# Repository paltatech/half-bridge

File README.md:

# TO247 Inverter power stage
This is the hardware repository of a 3 phase inverter, UNTESTED but designed with the following specs in mind:

* 70kw nominal, 150kw peak
* TO247 IGBT to allow for easy silicon upgrades and power capabilities. Its also cheaper.
* Watercooled
* Embedded security features (desaturation, soft turn off, reinforced isolation)

You can also check the layout [here](https://eyrie.io/board?id=7261e811b9074e0fb00fe3fcbbaa14d9) 

Will need some cnc milling, components, a pcb, and some spot welding

Made open source with open source tools (kicad, freecad)

## Bill of materials
BOM, pcb gerbers, and custom parts can be found in [fabrication files](https://bitbucket.org/paltatech/half-bridge) directory

## License
This documentation describes Open Hardware and is licensed under the CERN OHL v. 1.2

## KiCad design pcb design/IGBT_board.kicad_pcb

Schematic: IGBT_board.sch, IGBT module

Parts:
C1, C2, C3, C4, C5, C6, C7: 16uF 700v; CAP_FILM_EPCOS_42x20mm_3D_only; mfg# B32796G3166K
C51, C52: 4.7uF; CAPC2012X70
C77, C82: 100pF; CAPC1608X55
C85: 1uF; CAPC1608X55
D19: TVS; Diode-SMB_Standard; mfg# SMBJ24A
DS1: FAULT; LED-0603
DS2: PWR_GOOD; LED-0603
DS3: RESET; LED-0603
F1: FUSE; RESC3216X60; mfg# 0ZCJ0050AF2E
J1: CONN-100MIL-M-2x8; MPN 5103310-3
J5: PHASE CURRENT CONN; TE-292227-4; MPN 292227-4
MP1: HEATSINK; heatsink-watercooled-20x210mm
Q1, Q2, Q3, Q4, Q5, Q6, Q7, Q8, Q9, Q10, Q11, Q12: IGBT; TO-247-HV; mfg# IXXX110N65B4H1
R1, R2: 1R; RESC3225X60
R3, R4, R5, R6, R7, R8, R9, R10, R11, R12, R13, R14, R15, R16, R17, R18, R19, R20, R21, R22, R23, R24: 20R; RESC3225X60; mfg# CRCW251220R0FKEG
R51, R52, R53: 1k; RESC1608X50
R54, R56, R59, R61: 22R; RESC1608X50
SYM1: OSHW-SCHEM-PCB10mm; Logo_silk_OSHW_12x13mm
U5: LM1117IMP-v.v; SOT-223

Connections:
+5: C52.1, C85.2, J5.1, R51.1, R52.1, R53.1, U5.2, U5.4; also elsewhere on the board
+24: C51.1, D19.1, F1.2, U5.3; also elsewhere on the board
/FAULT: DS1.1, R61.2; also elsewhere on the board
/I_phase+: J1.2, J5.2
/I_phase-: J1.1, J5.3
/PWM_N: C77.1, R54.2; also elsewhere on the board
/PWM_P: C82.2, R59.2; also elsewhere on the board
/PWR_GOOD: DS2.1; also elsewhere on the board
/RESET: DS3.1, R56.1; also elsewhere on the board
/SYNC: J1.8; also elsewhere on the board
/TEMP: J1.9
/VEE_CTRL: J1.7; also elsewhere on the board
/V_phase+: J1.4; also elsewhere on the board
/V_phase-: J1.3; also elsewhere on the board
GATE_HIGH: R1.1, R2.1, R5.1, R6.1, R9.1, R10.1, R13.1, R14.1, R17.1, R18.1, R21.1, R22.1; also elsewhere on the board
GATE_LOW: R3.1, R4.1, R7.1, R8.1, R11.1, R12.1, R15.1, R16.1, R19.1, R20.1, R23.1, R24.1; also elsewhere on the board
GND: C51.2, C52.2, C77.2, C82.1, C85.1, D19.2, J1.10, J1.14, J1.16, J5.4, U5.1; also elsewhere on the board
unnamed: DS1.2, R51.2
unnamed: DS2.2, R52.2
unnamed: DS3.2, R53.2
unnamed: F1.1, J1.13, J1.15
unnamed: J1.5, R56.2
unnamed: J1.6, R61.1
unnamed: J1.11, R59.1
unnamed: J1.12, R54.1
unnamed: Q1.1, R1.2, R2.2
unnamed: Q2.1, R3.2, R4.2
unnamed: Q3.1, R5.2, R6.2
unnamed: Q4.1, R7.2, R8.2
unnamed: Q5.1, R9.2, R10.2
unnamed: Q6.1, R11.2, R12.2
unnamed: Q7.1, R13.2, R14.2
unnamed: Q8.1, R15.2, R16.2
unnamed: Q9.1, R17.2, R18.2
unnamed: Q10.1, R19.2, R20.2
unnamed: Q11.1, R21.2, R22.2
unnamed: Q12.1, R23.2, R24.2
PHASE: Q1.3, Q2.2, Q3.3, Q4.2, Q5.3, Q6.2, Q7.3, Q8.2, Q9.3, Q10.2, Q11.3, Q12.2; also elsewhere on the board
VBUS+: Q1.2, Q3.2, Q5.2, Q7.2, Q9.2, Q11.2; also elsewhere on the board
VBUS-: Q2.3, Q4.3, Q6.3, Q8.3, Q10.3, Q12.3; also elsewhere on the board

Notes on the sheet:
Highest performance IGBT I found: AUIRGPS4067D1 reasonable performance: IXXX110N65B4H1 tesla used IKW75N60TFKSA1
The plan is to design it for 70kw continuous, 200kw peak So, at 400v you need 175 Amp per phase (70kw current x 2.5). That is 30A per IGBT At 30A, 0.9v Vce = 27W per transistor aim to 50-50 power losses (switching and sat) At 45°C ambient temperature, if we want 75°C Junction temp, its a 30°C dT, a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
Sil-pad thermal: SPK4-0.006-00-11.512 kapton? hard anodized aluminum? gel immersion? (could help with igbt-heatsink cleareances)
Capacitors must be able to supply roughly 65% of battery supplied current, so its important to have enough rms current in the cap bank. In this case, if we plan for 200kW at 500A, we should expect a total RMS current of 325A in the capacitors. We have 16uF*7*3 = 336uF 14Arms per cap -> 98Arms per m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
For BOM creator: kicad_bom_wizard "%I" "%O.csv" "CSV"
(FILM)
PHASE LEG IGBT MODULE
deadtime calculation: * input filter * igbt driver: 30ns(skew)+25ns(rise/fall delta) + * boost transistor: * IGBT:
Rg < Rgdriver / N / 10 for lower Rg mismatch
Use common mode chokes?

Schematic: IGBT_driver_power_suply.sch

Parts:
C17: 1uF; CAPC1608X55
C18: 22nF; CAPC1608X55
C19: 22uF 16v; CAPC2012X70
C20: 1nF; CAPC1608X55
C21: 470pF; CAPC1608X55
C22, C23, C24, C25, C26, C27, C53, C54: 10uF 50v; CAPC3216X70; mfg# CL31A106KBHNNNE
C28, C29, C30, C31: 100nF 50v; CAPC2012X70; mfg# 08055C104JAT2A
C32, C33, C34, C35, C45: 47uF 50v; c_elec_6.3x7.7; mfg# EEE-FK1H470XP
C50: 100pF; CAPC1608X55
D5, D6, D7, D8, D9, D10, D22, D23: RB160MM-60TR; SOD-123F; mfg# RB160MM-60TR
DZ2: MM3Z12VB; SOD-323F; mfg# MM3Z12VB
Q15, Q16: CSD19533Q5A; TEXAS-Q5A; mfg# CSD19533Q5A
R34, R37: 0R; RESC1608X50
R35: 26.7k; RESC1608X50
R36, R40: 1.15k; RESC1608X50
R38, R39: 22R; RESC1608X50
R41: 0.22R; RESC3216X60
T1: TRANS-3-1CT; wurth_750342312; mfg# 750342312
TP1: SW1; TEST-SMD-SMALL
TP2: SW2; TEST-SMD-SMALL
TP6: 24v; TEST-SMD-SMALL
TP7, TP10: 15v; TEST-SMD-SMALL
TP8, TP11: GND; TEST-SMD-SMALL
TP9, TP12: -15v; TEST-SMD-SMALL
U2: LM5030; TSSOP-10_3x3mm_Pitch0.5mm; mfg# LM5030MM/NOPB

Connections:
+24: C45.1, R34.2, R36.1, T1.3, TP6.1; also elsewhere on the board
/IGBT_driver_BOT/+15V: C26.1, C30.1, C34.1, D7.1, TP10.1; also elsewhere on the board
/IGBT_driver_BOT/-15V: C27.2, C31.2, C35.2, D23.2, TP12.1; also elsewhere on the board
/IGBT_driver_TOP/+15V: C24.1, C28.1, C32.1, D5.1, TP7.1; also elsewhere on the board
/IGBT_driver_TOP/-15V: C25.2, C29.2, C33.2, D22.2, TP9.1; also elsewhere on the board
/SYNC: C50.1; also elsewhere on the board
/isolated power supply/CS: C21.1, R40.2, U2.8
GND: C17.1, C18.1, C19.2, C20.2, C21.2, C45.2, DZ2.2, R35.2, R41.2, U2.2, U2.7; also elsewhere on the board
unnamed: C17.2, R34.1, U2.1
unnamed: C18.2, U2.10
unnamed: C19.1, DZ2.1, R36.2, U2.4
unnamed: C20.1, R37.2
unnamed: C22.1, D5.2, D6.1
unnamed: C22.2, C53.2, T1.13
unnamed: C23.1, D7.2, D8.1
unnamed: C23.2, C54.2, T1.8
unnamed: C50.2, R35.1, U2.9
unnamed: C53.1, D9.2, D22.1
unnamed: C54.1, D10.2, D23.1
unnamed: Q15.1, Q15.2, Q15.3, Q16.1, Q16.2, Q16.3, R40.1, R41.1
unnamed: Q15.4, R38.1
unnamed: Q15.5, Q15.6, Q15.7, Q15.8, T1.5, TP1.1
unnamed: Q16.4, R39.2
unnamed: Q16.5, Q16.6, Q16.7, Q16.8, T1.1, TP2.1
unnamed: R37.1, U2.3
unnamed: R38.2, U2.5
unnamed: R39.1, U2.6
PHASE: C24.2, C25.1, C28.2, C29.1, C32.2, C33.1, D6.2, D9.1, T1.14, TP8.1; also elsewhere on the board
VBUS-: C26.2, C27.1, C30.2, C31.1, C34.2, C35.1, D8.2, D10.1, T1.7, TP11.1; also elsewhere on the board

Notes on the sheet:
Power calculation according to http://www.ti.com/lit/ug/tidu355a/tidu355a.pdf 0.6W+(0.000000183C*6)*20000Hz*(15v+8v)+(0.000000005500F*6)*20000Hz*(15v+8v)^2 = 1.45 W
Left side corresponds to http://www.ti.com/lit/ug/tidu355a/tidu355a.pdf Right side corresponds to TIDUA15A
Dual Isolated +15v -15v power supply 2W per IGBT bank
check MGJ2D241509SC
Controlling pwm from MCU could help with harmonics, or maybe sync it with the leg switching freq
Always check the actual capacitance you get at the operating voltage. These curves are for samsung's MLCC caps
weird way to draw a transformer... fix it
About syncing: * External source frequency must be higher than configured frequency (configured with RT) * 15nsec to 150nsec pulse width * 1.5V to 3.0V signal amplitude Why syncing? Phase voltage sampling could be measured at the same point in the power supply ripple. You can avoid switching the su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
Frequency setting with RT. R = (1/F - 172E-9) / 182e-12 So, eval board was switching at 200khz. Figure out why, this transformer is supposed to be operated at 500khz
10k ohm would set this to 500KHz...
For +15/-8v operation, short C53/C54 and remove D9/D10
Ensure <30pF transformer capacitance Less in case of SiC drives.where 5pF will inject 250mA at 50V/ns (dV/dt) in the control side. Adding mounting point for grounding these switching currents to the chassis so they don't travel across control wiring.

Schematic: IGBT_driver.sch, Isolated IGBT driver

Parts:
C8, C83: 100nF; CAPC1608X55
C9, C10, C11: 1uF 50v; CAPC2012X70; mfg# CL21B105KBFNNNE
C12, C13, C57, C58, C71, C72: 10uF 50v; CAPC3216X70; mfg# CL31A106KBHNNNE
C14, C15: 100nF 50v; CAPC2012X70; mfg# 08055C104JAT2A
C16: 100pF COG; CAPC2012X70; mfg# C0805C101J5GACTU
C46: 10uF; CAPC1608X55
C47: 5nF 50v; CAPC2012X70
C55: 1nF; CAPC1608X55
C56: 1uF; CAPC1608X55
C87: 10nF; CAPC1608X55
D1, D16: SK310A-LTP; do214ac; mfg# SK310A-LTP
D2: RB168MM-60TR; SOD-123F; mfg# RB168MM-60TR
D3, D4: MURS160-13-F; Diode-SMB_Standard; mfg# MURS160-13-F
D15: 1N4148W; SOD-123
D17: GSOT03C; SOT-23; mfg# GSOT03C-E3-08
D25: ES2J-LTP; DIOM5226X203; MPN ES2J-LTP
DZ1: MM3Z12VB; SOD-323F; mfg# MM3Z12VB
DZ5: SMCJ440CA; DIOM7959X265; MPN SMCJ440CA
J2: DESAT; CONN-100MIL-F-1x1
Q13: NPN; DPAK-2; mfg# MJD3055T4G
Q14: PNP; DPAK-2; mfg# MJD2955T4G
R25, R26: 10k; RESC1608X50
R27: 10R; RESC1608X50
R28: 4.7k; RESC1608X50
R29, R30: 12R; RESC2012X50
R31, R32: 3R; RESC6432X70; mfg# PCNM2512K3R00FST5
R33: 1k; RESC2012X50
R58: 1k; RESC1608X50
R60: 4.7k; RESC2012X50
R62: 12R; RESC1608X50; mfg# RC0603FR-07390RL
R68, R93: 390R; RESC1608X50; mfg# RC0603FR-07390RL
R69: NI; RESC6432X70
R75: NI; RESC6432X70; MPN PCNM1206K2R00FST5
TP3: IN; TEST-SMD-SMALL
TP4: GND; TEST-SMD-SMALL
U1: ISO5852S; SOIC-16_7.5x10.3mm_Pitch1.27mm; mfg# ISO5852SQDWRQ1
U8: SI8710B; SDIP6; mfg# SI8710BD-B-IS
U13: LM3480; SOT-23; mfg# LM3480IM3X-12/NOPB

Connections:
+5: C46.1, R25.1, R26.1, R27.1; also elsewhere on the board
/FAULT: D15.1, R25.2, U1.13; also elsewhere on the board
/IGBT_driver_TOP/12.0V: C56.1, R68.2, U8.6 (VCC), U13.1 (OUT)
/IGBT_driver_TOP/+15V: C10.1, C12.1, C14.1, C57.1, C71.1, C83.1, D16.1, Q13.2, U1.5, U13.2 (IN); also elsewhere on the board
/IGBT_driver_TOP/-VEE: C9.2, C11.2, C13.2, C15.2, C58.2, C72.2, C87.2, D1.2, Q14.2, U1.1, U1.8; also elsewhere on the board
/IGBT_driver_TOP/supply control/PWM: R68.1, U8.5 (Vo); also elsewhere on the board
/PWM_N: D17.2, R28.1, U1.11; also elsewhere on the board
/PWM_P: D15.2, D17.1, R58.1, TP3.1, U1.10; also elsewhere on the board
/PWR_GOOD: R26.2, U1.12; also elsewhere on the board
/RESET: C55.1, U1.14; also elsewhere on the board
/VEE_CTRL: R93.2; also elsewhere on the board
GATE_HIGH: C47.1, D1.1, D16.2, D25.1, R31.1, R32.1, R60.2, R69.1, R75.1; also elsewhere on the board
GND: C8.2, C46.2, C55.2, D17.3, R28.2, R58.2, TP4.1, U1.9, U1.16, U8.3 (K); also elsewhere on the board
unnamed: C8.1, R27.2, U1.15
unnamed: C16.1, D2.1, DZ1.1, R33.2, U1.2
unnamed: C87.1, R62.1
unnamed: D3.1, D4.2
unnamed: D3.2, R33.1
unnamed: D25.2, DZ5.2
unnamed: Q13.1, Q14.1, R29.1, R30.1
unnamed: Q13.3, R31.2, R69.2
unnamed: Q14.3, R32.2, R75.2
unnamed: R29.2, U1.4
unnamed: R30.2, R62.2, U1.6
unnamed: R93.1, U8.1 (A)
PHASE: C9.1, C10.2, C11.1, C12.2, C13.1, C14.2, C15.1, C16.2, C47.2, C56.2, C57.2, C58.1, C71.2, C72.1, C83.2, D2.2, DZ1.2, R60.1, U1.3, U8.4 (GND), U13.3; also elsewhere on the board
VBUS+: D4.1, DZ5.1, J2.1; also elsewhere on the board

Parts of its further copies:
C36, C84: 100nF; CAPC1608X55
C37, C38, C39: 1uF 50v; CAPC2012X70; mfg# CL21B105KBFNNNE
C40, C41, C65, C66, C73, C74: 10uF 50v; CAPC3216X70; mfg# CL31A106KBHNNNE
C42, C43: 100nF 50v; CAPC2012X70; mfg# 08055C104JAT2A
C44: 100pF COG; CAPC2012X70; mfg# C0805C101J5GACTU
C48: 10uF; CAPC1608X55
C49: 5nF 50v; CAPC2012X70
C63: 1nF; CAPC1608X55
C64: 1uF; CAPC1608X55
C86: 10nF; CAPC1608X55
D11, D18: SK310A-LTP; do214ac; mfg# SK310A-LTP
D12: RB168MM-60TR; SOD-123F; mfg# RB168MM-60TR
D13, D14: MURS160-13-F; Diode-SMB_Standard; mfg# MURS160-13-F
D20: 1N4148W; SOD-123
D21: GSOT03C; SOT-23; mfg# GSOT03C-E3-08
D24: ES2J-LTP; DIOM5226X203; MPN ES2J-LTP
DZ3: MM3Z12VB; SOD-323F; mfg# MM3Z12VB
DZ4: SMCJ440CA; DIOM7959X265; MPN SMCJ440CA
J3: DESAT; CONN-100MIL-F-1x1
Q17: NPN; DPAK-2; mfg# MJD3055T4G
Q18: PNP; DPAK-2; mfg# MJD2955T4G
R42, R43: 10k; RESC1608X50
R44: 10R; RESC1608X50
R45: 4.7k; RESC1608X50
R46, R47: 12R; RESC2012X50
R48, R49: 3R; RESC6432X70; mfg# PCNM2512K3R00FST5
R50: 1k; RESC2012X50
R55: 12R; RESC1608X50; mfg# RC0603FR-07390RL
R57: 1k; RESC1608X50
R67: 4.7k; RESC2012X50
R74, R94: 390R; RESC1608X50; mfg# RC0603FR-07390RL
R89: NI; RESC6432X70
R90: NI; RESC6432X70; MPN PCNM1206K2R00FST5
TP13: IN; TEST-SMD-SMALL
TP14: GND; TEST-SMD-SMALL
U3: ISO5852S; SOIC-16_7.5x10.3mm_Pitch1.27mm; mfg# ISO5852SQDWRQ1
U11: SI8710B; SDIP6; mfg# SI8710BD-B-IS
U14: LM3480; SOT-23; mfg# LM3480IM3X-12/NOPB

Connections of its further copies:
+5: C48.1, R42.1, R43.1, R44.1; also elsewhere on the board
/FAULT: D20.1, R42.2, U3.13; also elsewhere on the board
/IGBT_driver_BOT/12.0V: C64.1, R74.2, U11.6 (VCC), U14.1 (OUT)
/IGBT_driver_BOT/+15V: C38.1, C40.1, C42.1, C65.1, C73.1, C84.1, D18.1, Q17.2, U3.5, U14.2 (IN); also elsewhere on the board
/IGBT_driver_BOT/-VEE: C37.2, C39.2, C41.2, C43.2, C66.2, C74.2, C86.2, D11.2, Q18.2, U3.1, U3.8; also elsewhere on the board
/IGBT_driver_BOT/supply control/PWM: R74.1, U11.5 (Vo); also elsewhere on the board
/PWM_N: D20.2, D21.1, R57.1, TP13.1, U3.10; also elsewhere on the board
/PWM_P: D21.2, R45.1, U3.11; also elsewhere on the board
/PWR_GOOD: R43.2, U3.12; also elsewhere on the board
/RESET: C63.1, U3.14; also elsewhere on the board
/VEE_CTRL: R94.2; also elsewhere on the board
GATE_LOW: C49.1, D11.1, D18.2, D24.1, R48.1, R49.1, R67.2, R89.1, R90.1; also elsewhere on the board
GND: C36.2, C48.2, C63.2, D21.3, R45.2, R57.2, TP14.1, U3.9, U3.16, U11.3 (K); also elsewhere on the board
unnamed: C36.1, R44.2, U3.15
unnamed: C44.1, D12.1, DZ3.1, R50.2, U3.2
unnamed: C86.1, R55.1
unnamed: D13.1, D14.2
unnamed: D13.2, R50.1
unnamed: D24.2, DZ4.2
unnamed: Q17.1, Q18.1, R46.1, R47.1
unnamed: Q17.3, R48.2, R89.2
unnamed: Q18.3, R49.2, R90.2
unnamed: R46.2, U3.4
unnamed: R47.2, R55.2, U3.6
unnamed: R94.1, U11.1 (A)
PHASE: D14.1, DZ4.1, J3.1; also elsewhere on the board
VBUS-: C37.1, C38.2, C39.1, C40.2, C41.1, C42.2, C43.1, C44.2, C49.2, C64.2, C65.2, C66.1, C73.2, C74.1, C84.2, D12.2, DZ3.2, R67.1, U3.3, U11.4 (GND), U14.3; also elsewhere on the board

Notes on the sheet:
ISO5852S isolated gate driver with current buffering
5kV RMS Isolation barrier
Gate resistor power rating: Check www.goo.gl/HwrKMw Its around 2.5W ON (and we have up to 8W) and 0.6W OFF (and we have up to 8W). (8W in an ideal pcb layout that we won't have) Try to find something like this http://www.isabellenhuette.de/fileadmin/content/praezisions-leistungswiderstaende/SMP.PDF
TH to connect to copper collector layer
drive a 100 khz PWM
Keep decoupling caps close to the transistors
non-magnetic, pulse withstanding resistors!
When FAULT is asserted externally, mute the input
(blanking cap) With this cap you tune the desat response time. SiC mosfets need to enter soft turn off in less than 3us. IGBTs have larger parasitic capacitance so its not possible to use such short times. IGBTs can withstand almost 10us.
10 Ohm vishay resistors come in 0.1% 25ppm for the same price of 1% 100ppm 2 ohm
(50ns recovery time)
Latchup protection. A latchup here blows IGBTs
12V 200mW zener for protection
Ensures IGBT is OFF while driver is powered off
input protection. You don't want a latch-up here
High wattage, and hard to heatsink
20uA leakage at 125°C
Needed for soft turn-off when current boost is used (tiduc70a 2.1.7)
Active overvoltage clamping for high fault current turn-off
AEC Q-101: MJD44H11 and MJD45H11

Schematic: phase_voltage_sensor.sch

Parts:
C78, C80: 100nF; CAPC1608X55
C79: 330pF; CAPC1608X55
C81: 2.2uF; CAPC1608X55
DZ6: 5v; SOT-23; MPN BZX84-A5V1,215
J4: PHASE; CONN-100MIL-F-1x1
R82, R84: 1M; RESC3216X60; MPN CHV1206-FX-1004ELF
R83: 12R; RESC1608X50
R85, R88: 1k; RESC1608X50
U10: AMC1301; SOIC127P1032X265-8; MPN AMC1301DWVR

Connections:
+5: C80.1, C81.1, U10.8 (VDD2); also elsewhere on the board
/IGBT_driver_BOT/+15V: R83.2; also elsewhere on the board
/V_phase+: U10.7 (VOUTP); also elsewhere on the board
/V_phase-: U10.6 (VOUTN); also elsewhere on the board
/phase voltage/VIN+: C79.1, R84.1, R85.1, U10.2 (VINP)
/phase voltage/VIN-: C79.2, R88.2, U10.3 (VINN)
GND: C80.2, C81.2, U10.5 (GND2); also elsewhere on the board
unnamed: C78.2, DZ6.3, R83.1, U10.1 (VDD1)
unnamed: R82.1, R84.2
PHASE: J4.1, R82.2; also elsewhere on the board
VBUS-: C78.1, DZ6.1, R85.2, R88.1, U10.4 (GND1); also elsewhere on the board

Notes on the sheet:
=1000/(2000000+2000)*650*8.2 = 2.66V differential output at 650V
These particular 1206 resistors are rated at 800V each. Put slots though
0-650V phase voltage measurement using isolation amplifier
Route very close together

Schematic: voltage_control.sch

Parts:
C67, C69: 10nF; CAPC1608X55
C68: 100nF; CAPC1608X55
C70: 47uF 50v; c_elec_6.3x7.7; mfg# EEE-FK1H470XP
C75: 10uF 50v; CAPC3216X70; mfg# CL31A106KBHNNNE
Q19: PNP; DPAK-2; mfg# MJD2955T4G
R73: 100R; RESC2012X50
R76, R77, R78: 10k; RESC1608X50
U12: OPA2172; SOIC127P600X175-8; MPN OPA2172IDR

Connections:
/IGBT_driver_BOT/+15V: C68.2, U12.8; also elsewhere on the board
/IGBT_driver_BOT/-15V: C68.1, U12.4; also elsewhere on the board
/IGBT_driver_BOT/-VEE: C70.2, U12.6; also elsewhere on the board
/IGBT_driver_BOT/supply control/PWM: R76.2; also elsewhere on the board
/IGBT_driver_TOP/-15V: Q19.2; also elsewhere on the board
/IGBT_driver_TOP/-VEE: C75.1, Q19.3; also elsewhere on the board
unnamed: C67.1, R76.1, R77.2, U12.2
unnamed: C67.2, R77.1, R78.2, U12.1
unnamed: C69.2, R78.1, U12.5
unnamed: Q19.1, R73.1
unnamed 100: R73.2; also elsewhere on the board
unnamed 101: U12.7; also elsewhere on the board
PHASE: C75.2; also elsewhere on the board
VBUS-: C69.1, C70.1, U12.3; also elsewhere on the board

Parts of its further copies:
C59, C61: 10nF; CAPC1608X55
C60: 100nF; CAPC1608X55
C62: 47uF 50v; c_elec_6.3x7.7; mfg# EEE-FK1H470XP
C76: 10uF 50v; CAPC3216X70; mfg# CL31A106KBHNNNE
Q20: PNP; DPAK-2; mfg# MJD2955T4G
R70, R71, R72: 10k; RESC1608X50
R79: 100R; RESC2012X50
U9: OPA2172; SOIC127P600X175-8; MPN OPA2172IDR

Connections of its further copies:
/IGBT_driver_BOT/-15V: Q20.2; also elsewhere on the board
/IGBT_driver_BOT/-VEE: C76.1, Q20.3; also elsewhere on the board
/IGBT_driver_TOP/+15V: C60.2, U9.8; also elsewhere on the board
/IGBT_driver_TOP/-15V: C60.1, U9.4; also elsewhere on the board
/IGBT_driver_TOP/-VEE: C62.2, U9.6; also elsewhere on the board
/IGBT_driver_TOP/supply control/PWM: R70.2; also elsewhere on the board
unnamed: C59.1, R70.1, R71.2, U9.2
unnamed: C59.2, R71.1, R72.2, U9.1
unnamed: C61.2, R72.1, U9.5
unnamed: Q20.1, R79.1
unnamed 100: U9.7; also elsewhere on the board
unnamed 101: R79.2; also elsewhere on the board
PHASE: C61.1, C62.1, U9.3; also elsewhere on the board
VBUS-: C76.2; also elsewhere on the board

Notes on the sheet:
+-75mA output
Simulation: step response (0->90%) in 0.4msec 100kHz PWM
Negative power supply programmable with PWM
0% duty -> -1V 100% duty -> - 9V
Try to heatsink this pnp
AD8397 drives more current

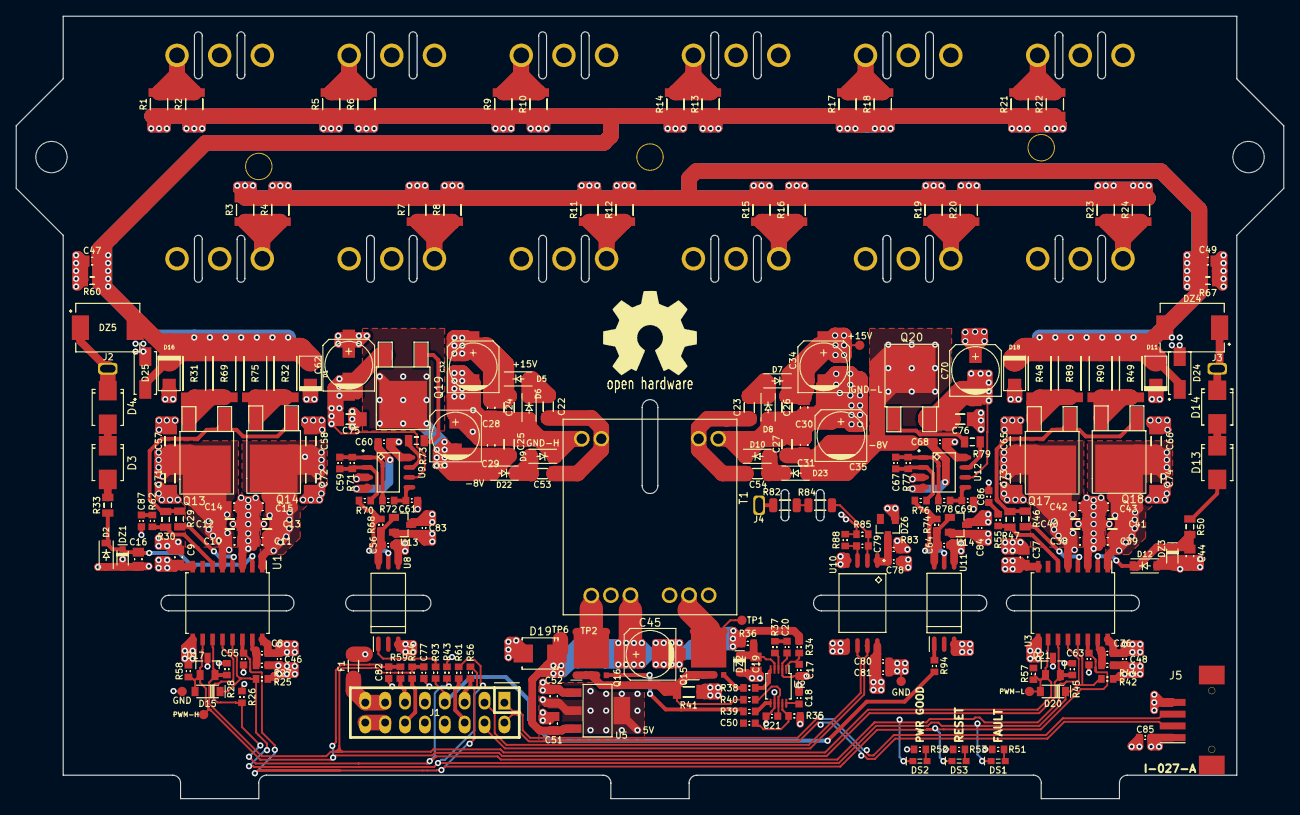
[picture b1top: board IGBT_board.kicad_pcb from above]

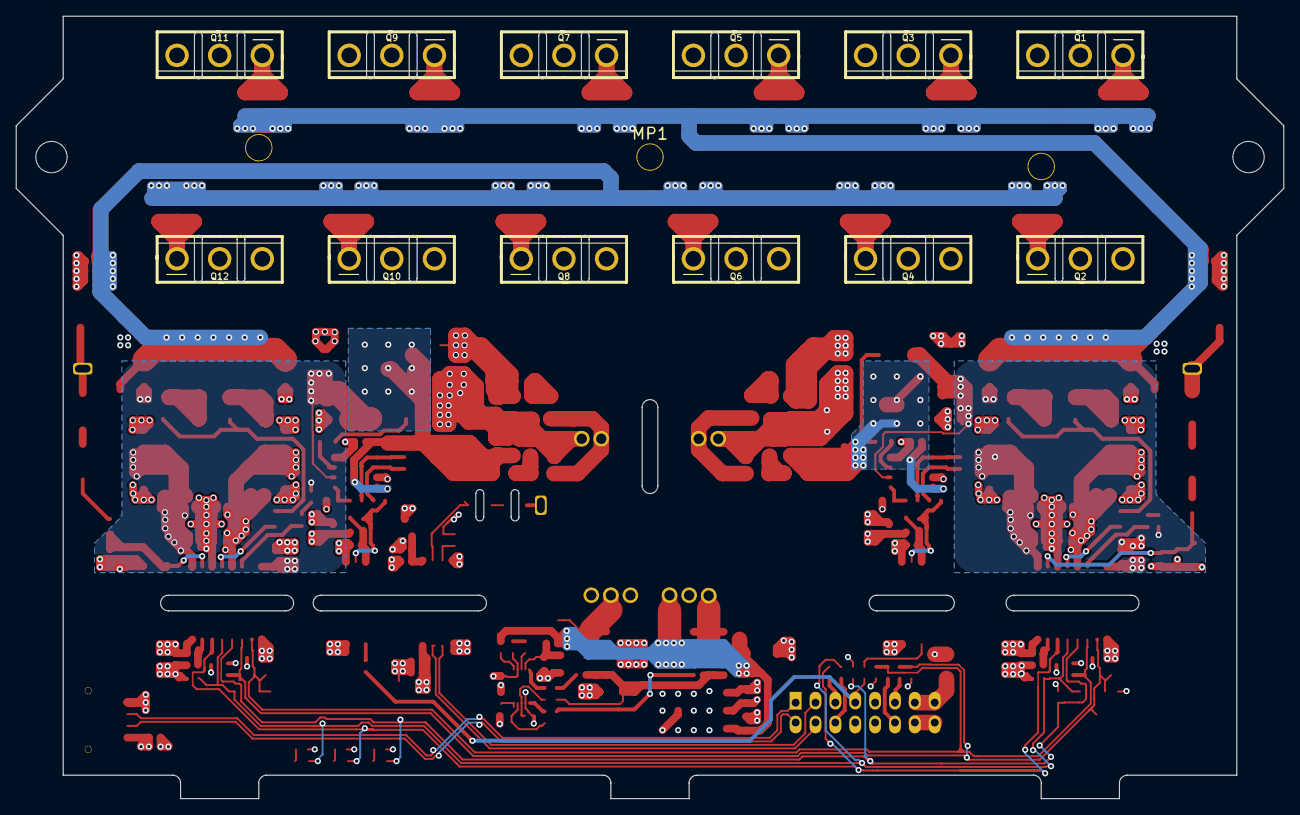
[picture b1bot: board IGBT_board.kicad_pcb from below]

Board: 4 copper layers, 162.0 x 100.0 mm, 259 parts (20 on the bottom side), 107 nets.

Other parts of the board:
eREF**: MountingHole_6mm; MountingHole_4mm

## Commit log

2016-10-28 First commit. Added cpavlina libraries and .gitignore
2016-10-28 Added working directories
2016-11-04 Added schematic of power transistors and caps, basic layout and watercooling
2016-11-06 Draft of bus bars and mounting points
2016-11-09 Added IGBT gate driver circuit and isolated power supply
2016-11-12 Add some datasheets
2016-11-12 Add footprints, more layout and graphics
2016-11-20 Add IGBT driver datasheet
2016-11-20 Larger gate resistors, added gate caps, added comments and images to the schematic
2016-11-21 Added schottky between gate and 15v supply
2016-11-22 Updated 3D assembly. Copper cutouts, current transducer, updated pcb
2016-11-22 Added readme
2016-11-22 Added images
2016-11-23 Added 3D models, connector, more layout, updated readme
2016-11-23 Added testpoints
2016-11-24 Change gate diode direction, I thought Ron should be smaller than Roff, and its not
2016-11-24 Added NAND gates for shoot-through protection, and to configure the driver so when a fault is asserted the whole inverter will be shut down until a reset signal is issued
2016-11-26 Updated viable IGBT part#, selected infineon IGBT as project default
2016-11-26 Changed GND copper plane to avoid coupling between phase output and controller GND (112pF->13pF)
2016-11-26 Added on board 3.3v regulator, power supply fuse and some resistors to protect digital lines
2016-11-26 Added board dimensions and improved gate return path
2016-11-27 Update 3D assembly with smaller phase copper sheet
2016-11-27 Sync layout with schematic
2016-11-27 Fixed schematic label and more layout
2016-11-28 Updated cached library
2016-12-18 Added gate voltage control, more decoupling pads for the buffer transistors, added notes
2016-12-20 Better layout. Added 3d models and updated cache lib
2016-12-20 Removed old comments, added notes, connected programmable -VEE
2016-12-21 Updated copper planes. Added vias
2016-12-21 Improved gate traces using 4 layers. Increased TO-247 creepage with slots
2016-12-21 Added phase voltage sensing
2016-12-21 Connected phase sensing, added images
2016-12-22 Phase voltage sensing laid out
2016-12-24 Added mounting points, trying 12 pos connector. Added 3d models
2016-12-26 Updated gate resistor rating, qty and part#, updated desat blocking diode with much beetter recovery time
2016-12-26 Updated cache.lib file
2016-12-26 Added comments before I forget things, changed X5R to X7R. Updated PCB
2016-12-26 Forgot the cache-lib again
2016-12-27 Power supply sync input. And more comments
2016-12-30 Changed power supply from 15/-8V to +15/-15V se we can make better use uf programmable -VEE. Changed connector to 14pos. Connected some missing signals. Updated layout
2016-12-31 Changed isolated amplifier from AMC1200 to AMC1301 because it has reinforced isolation. This required a different layout
2017-01-10 More .step 3D models included for better portability
2017-01-10 For some reasong eyrie needs the schematics and cache file synced
2017-01-11 Larger 2512 gate resistors
2017-01-17 Added CERN Open Hardware Licence ("CERN OHL") version 1.2 documents
2017-02-10 Updated README and images
2017-02-10 Fixed README link
2017-02-10 Addded schematic image
2017-07-17 Added current sensor connector. Layout is now symmetrical
2018-11-12 Add gate driver load to enable 2 step turnoff in buffered configuration. Updated layout.

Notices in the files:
pcb design/IGBT_board.sch:
Copyright PALTA TECH S.A.
pcb design/IGBT_driver.sch:
Licensed under CERN OHL v.1.2 or later
